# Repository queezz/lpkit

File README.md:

# Langmuir Probe Kit
`lpkit` is a basket of tools to quickly get your plasma temperature and density from a fast sweep of voltage.
## 2025 Yokogawa SL1000
Using a signal generator, connected to an insulated amplifier, we record probe voltage and current. 

## PCB

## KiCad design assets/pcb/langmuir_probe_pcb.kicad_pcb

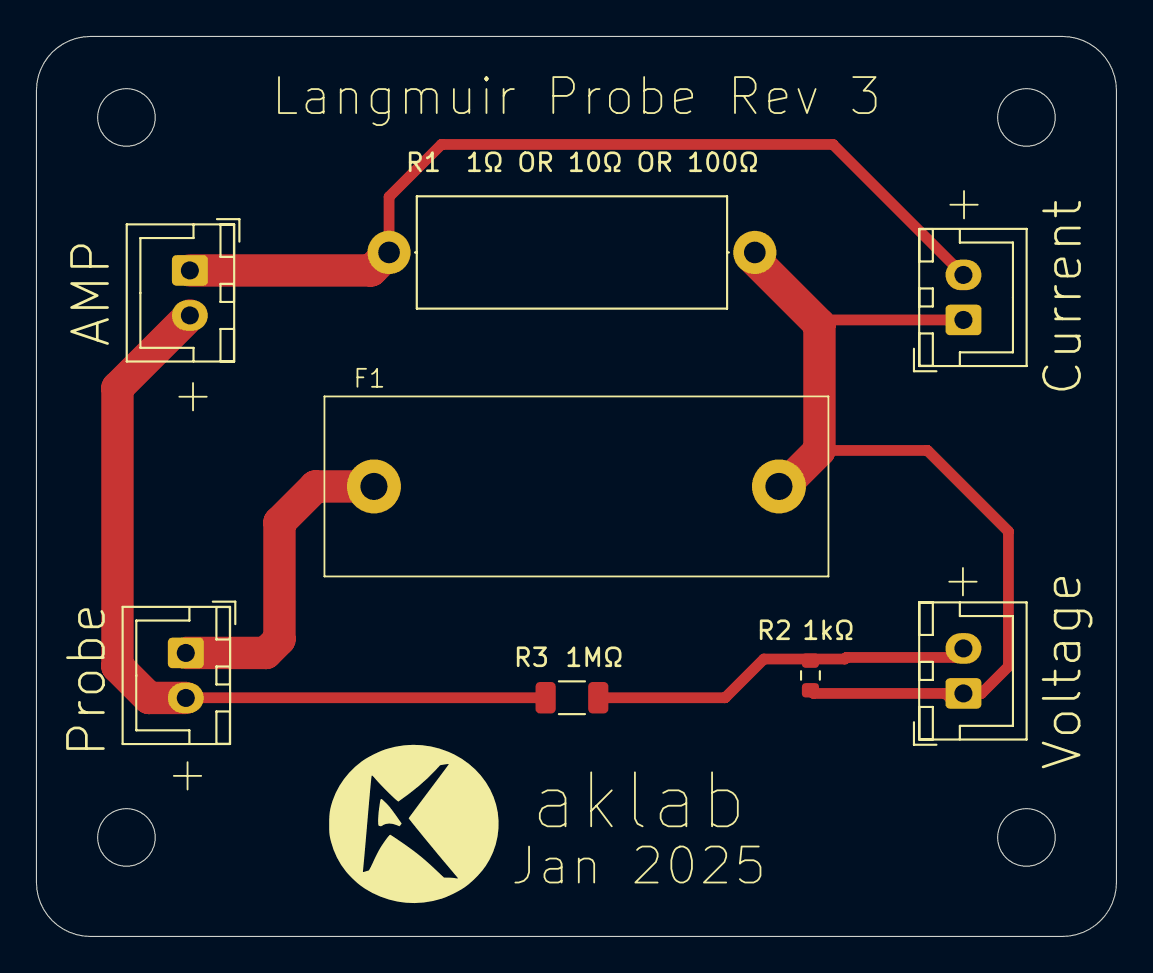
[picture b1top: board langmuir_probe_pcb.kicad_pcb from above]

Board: 2 copper layers, 60.0 x 50.0 mm, 12 parts (1 on the bottom side), 5 nets.

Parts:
AMP: JST_XH_B2B-XH-A_1x02_P2.50mm_Vertical
Current: JST_XH_B2B-XH-A_1x02_P2.50mm_Vertical
F1: Fuse; BLX-A Fuse Holder
H1, H2, H3, H4: MountingHole; MountingHole_3.2mm_M3
Probe: JST_XH_B2B-XH-A_1x02_P2.50mm_Vertical
R1: 100; R_Axial_DIN0617_L17.0mm_D6.0mm_P20.32mm_Horizontal
R2: 1k; R_0603_1608Metric
R3: 1M; R_1206_3216Metric
Voltage: JST_XH_B2B-XH-A_1x02_P2.50mm_Vertical

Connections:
unnamed: AMP.2 (1), Probe.2 (1), R3.2
unnamed: AMP.1 (2), Current.2 (1), R1.1
unnamed: Current.1 (2), F1.2, R1.2, R2.2, Voltage.1 (2)
unnamed: F1.1, Probe.1 (2)
unnamed: R2.1, R3.1, Voltage.2 (1)

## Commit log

2025-02-05 removed unused xarray import
2025-02-05 Added Te calculation
2025-02-07 analysis update
2025-02-10 Analysis update: line + exponent
